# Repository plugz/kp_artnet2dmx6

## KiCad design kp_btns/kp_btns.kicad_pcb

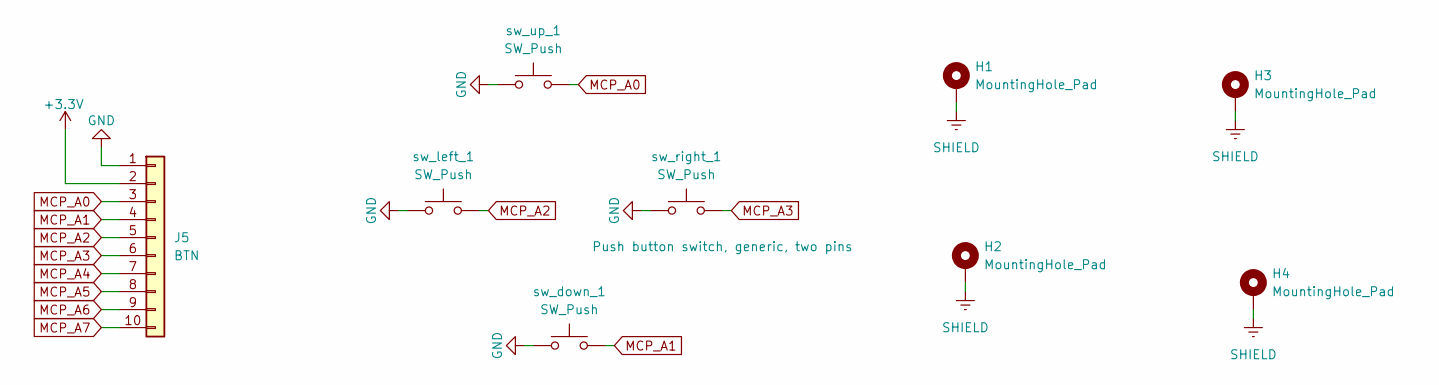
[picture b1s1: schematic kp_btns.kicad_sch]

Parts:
H1, H2, H3, H4: MountingHole_Pad; MountingHole_3.2mm_M3_Pad
J5: BTN; IDC-Header_2x05_P2.54mm_Vertical; JLCPCB Part # C5665
sw_down_1: SW_Push; SW_SPST_Omron_B3F-40xx
sw_left_1: SW_Push; SW_SPST_Omron_B3F-40xx
sw_right_1: SW_Push; SW_SPST_Omron_B3F-40xx
sw_up_1: SW_Push; SW_SPST_Omron_B3F-40xx

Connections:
+3.3V: J5.2
GND: J5.1, sw_down_1.1, sw_left_1.1, sw_right_1.1, sw_up_1.1
MCP_A0: J5.3, sw_up_1.2
MCP_A1: J5.4, sw_down_1.2
MCP_A2: J5.5, sw_left_1.2
MCP_A3: J5.6, sw_right_1.2
MCP_A4: J5.7
MCP_A5: J5.8
MCP_A6: J5.9
MCP_A7: J5.10
SHIELD: H1.1 (1_1), H2.1 (1_1), H3.1 (1_1), H4.1 (1_1)

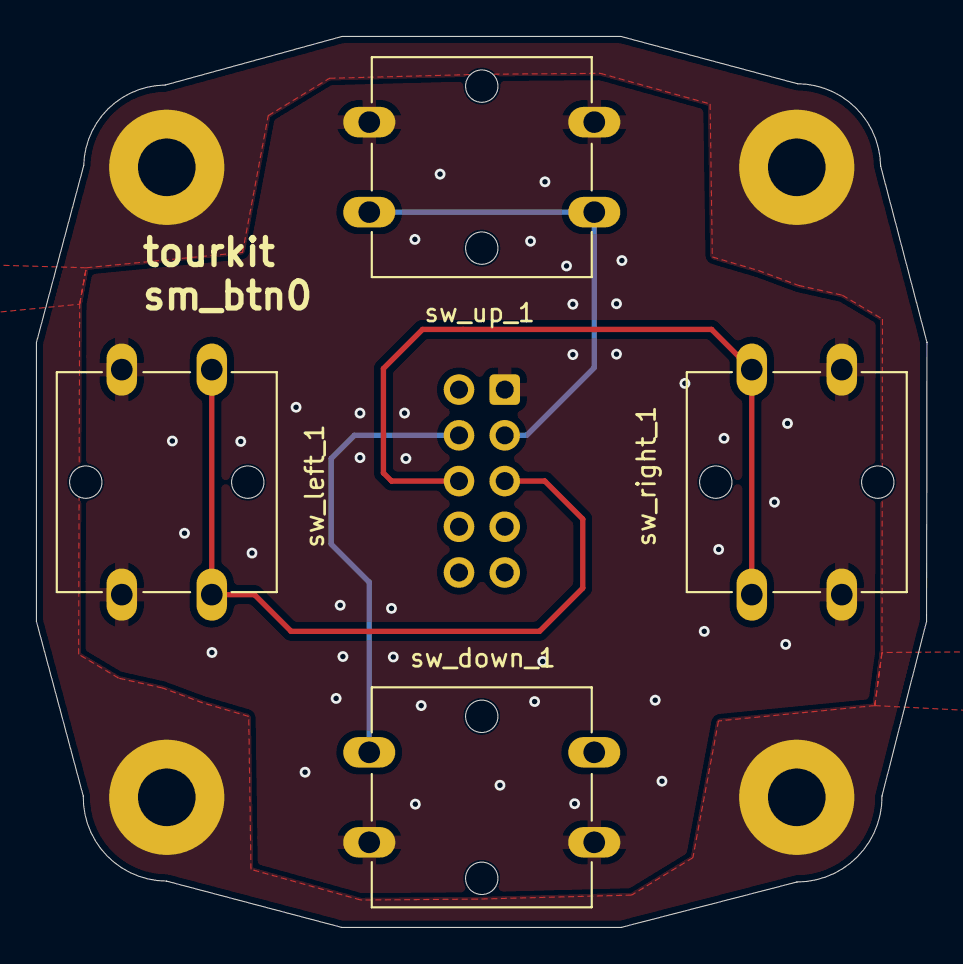
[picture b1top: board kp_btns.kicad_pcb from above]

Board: 2 copper layers, 49.5 x 49.5 mm, 9 parts (1 on the bottom side), 6 nets.

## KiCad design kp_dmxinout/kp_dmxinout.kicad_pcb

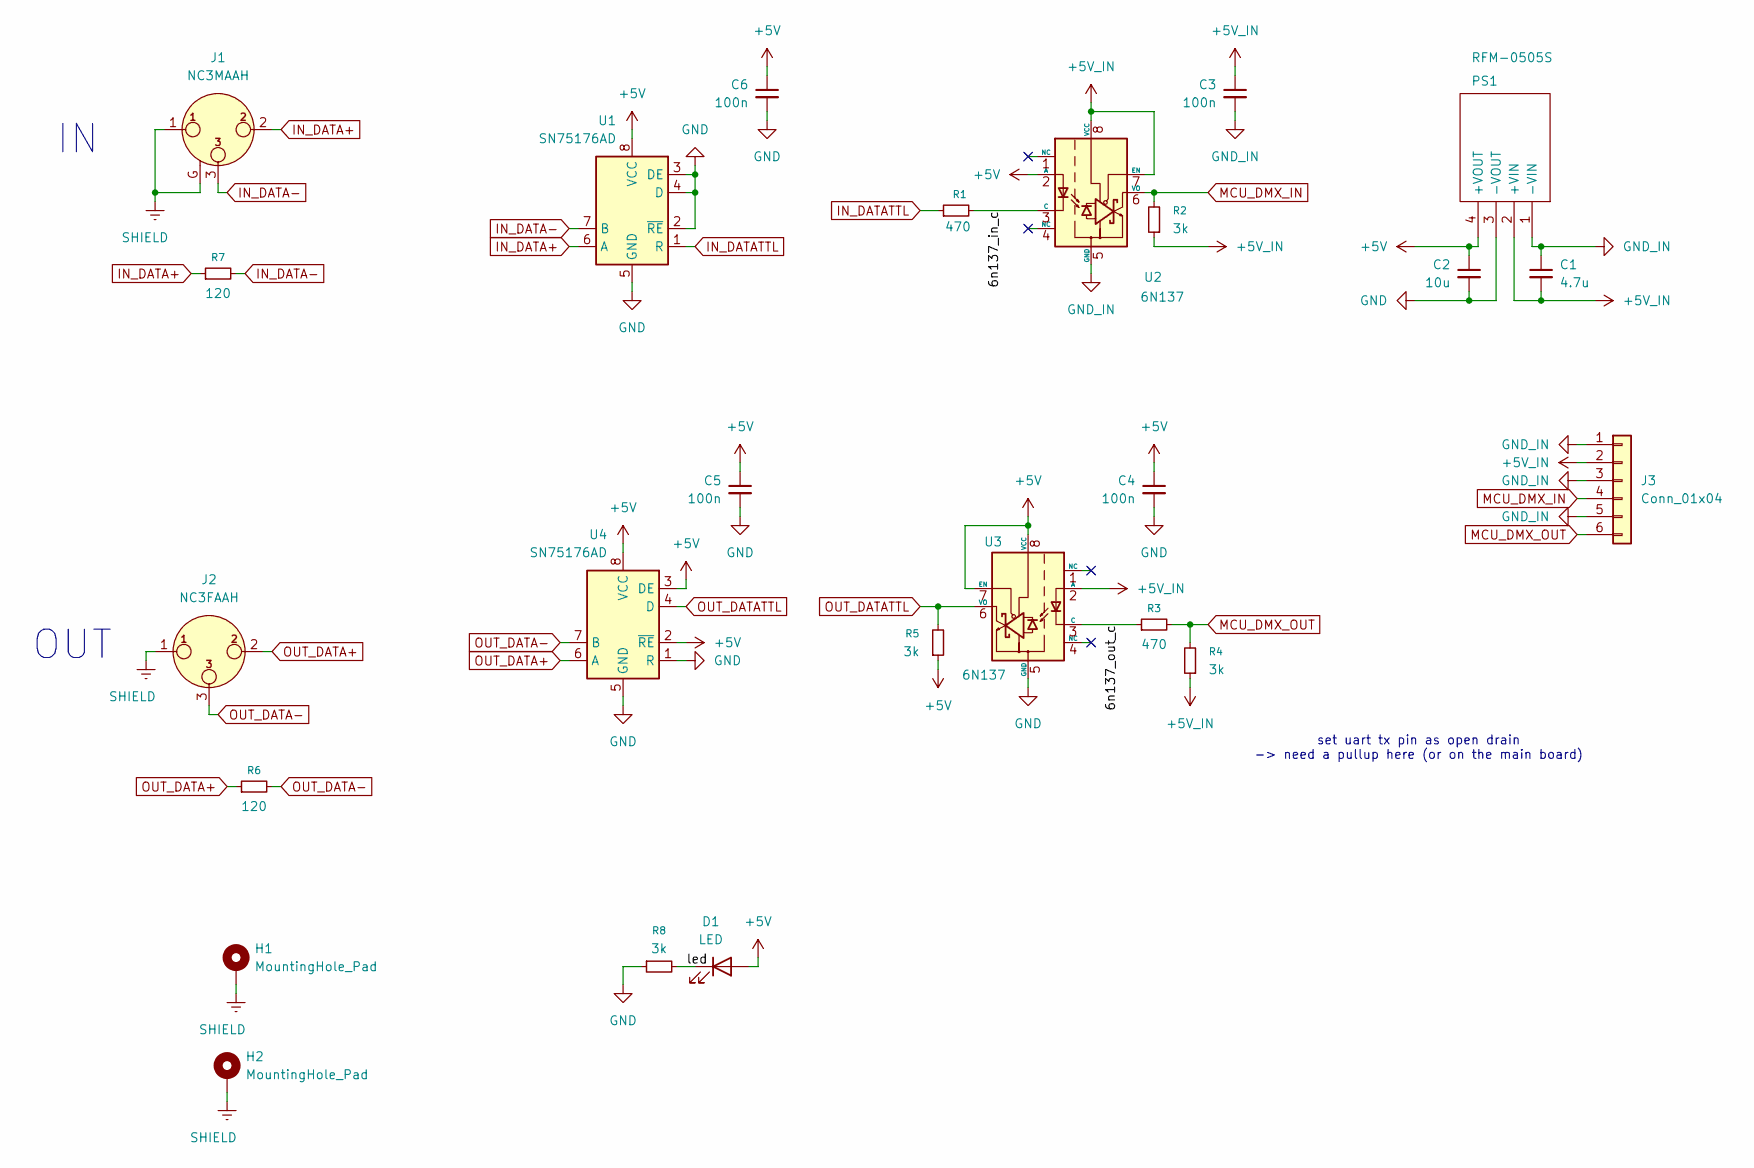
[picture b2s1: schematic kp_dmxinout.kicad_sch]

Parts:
C1: 4.7u; C_1206_3216Metric; LCSC C51205
C2: 10u; C_1206_3216Metric; LCSC C13585
C3, C4, C5, C6: 100n; C_0402_1005Metric; LCSC C1525
D1: LED; LED_0805_2012Metric; LCSC C965812
H1, H2: MountingHole_Pad; MountingHole_3.2mm_M3_Pad_Via
J1: NC3MAAH; Jack_XLR_Neutrik_NC3MAAH_Horizontal; LCSC C368463
J2: NC3FAAH; Jack_XLR_Neutrik_NC3FAAH_Horizontal; LCSC C368521
J3: Conn_01x04; IDC-Header_2x03_P2.54mm_Vertical; LCSC C11214
PS1: RFM-0505S; RFM0505S; Manufacturer_Part_Number RFM-0505S; LCSC C22371855
R1, R3: 470; R_0603_1608Metric; LCSC C844786
R2, R4, R5, R8: 3k; R_0805_2012Metric; LCSC C126350
R6, R7: 120; R_0603_1608Metric; LCSC C844736
U1, U4: SN75176AD; SOIC-8_3.9x4.9mm_P1.27mm; LCSC C468242
U2, U3: 6N137; DIP-8_W7.62mm; LCSC C142297

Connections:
+5V: C2.1, C4.1, C5.1, C6.1, D1.2 (A), PS1.4 (+VOUT), R5.1, U1.8 (VCC), U2.2 (A), U3.7 (EN), U3.8 (VCC), U4.2 (~RE), U4.3 (DE), U4.8 (VCC)
+5V_IN: C1.2, C3.1, J3.2, PS1.2 (+VIN), R2.1, R4.1, U2.7 (EN), U2.8 (VCC), U3.2 (A)
/6n137_in_c: R1.2, U2.3 (C)
/6n137_out_c: R3.1, U3.3 (C)
/led: D1.1 (K), R8.2
GND: C2.2, C4.2, C5.2, C6.2, PS1.3 (-VOUT), R8.1, U1.2 (~RE), U1.3 (DE), U1.4 (D), U1.5 (GND), U3.5 (GND), U4.1 (R), U4.5 (GND)
GND_IN: C1.1, C3.2, J3.1, J3.3, J3.5, PS1.1 (-VIN), U2.5 (GND)
IN_DATA+: J1.2, R7.1, U1.6 (A)
IN_DATA-: J1.3, R7.2, U1.7 (B)
IN_DATATTL: R1.1, U1.1 (R)
MCU_DMX_IN: J3.4, R2.2, U2.6 (VO)
MCU_DMX_OUT: J3.6, R3.2, R4.2
OUT_DATA+: J2.2, R6.1, U4.6 (A)
OUT_DATA-: J2.3, R6.2, U4.7 (B)
OUT_DATATTL: R5.2, U3.6 (VO), U4.4 (D)
SHIELD: H1.1 (1_1), H2.1 (1_1), J1.1, J1.G, J2.1

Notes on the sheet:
set uart tx pin as open drain -> need a pullup here (or on the main board)
OUT

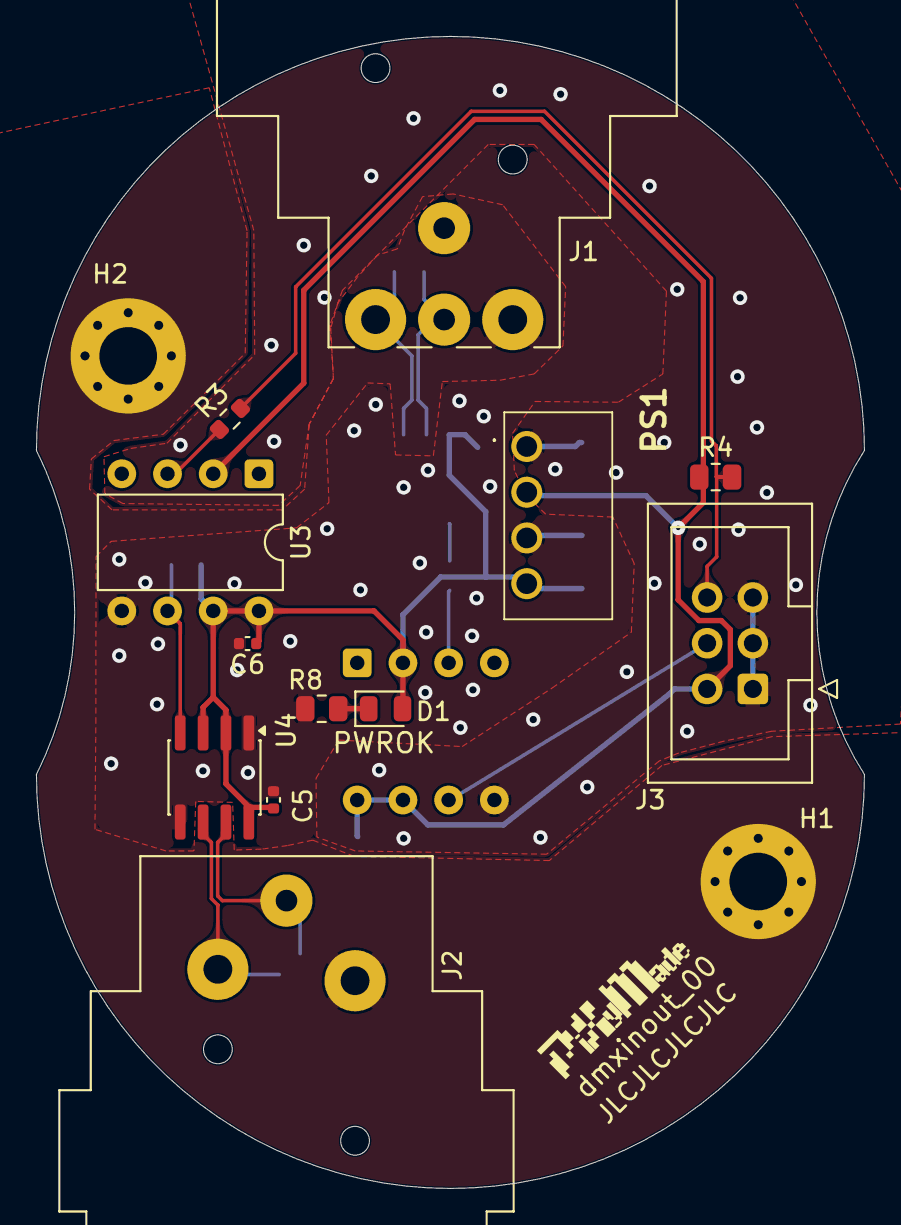
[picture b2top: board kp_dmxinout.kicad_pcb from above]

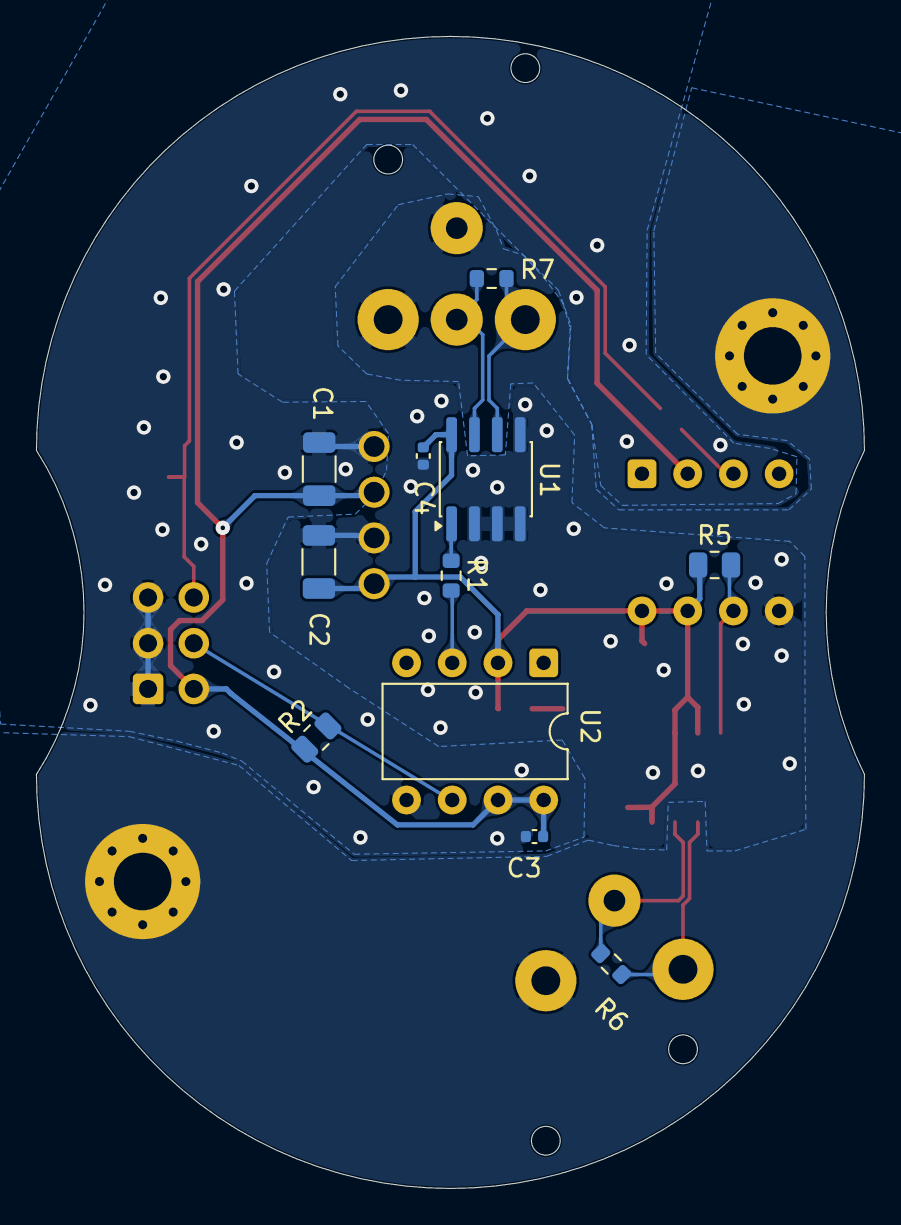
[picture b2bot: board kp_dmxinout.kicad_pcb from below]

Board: 2 copper layers, 46.0 x 64.0 mm, 25 parts (11 on the bottom side), 16 nets.

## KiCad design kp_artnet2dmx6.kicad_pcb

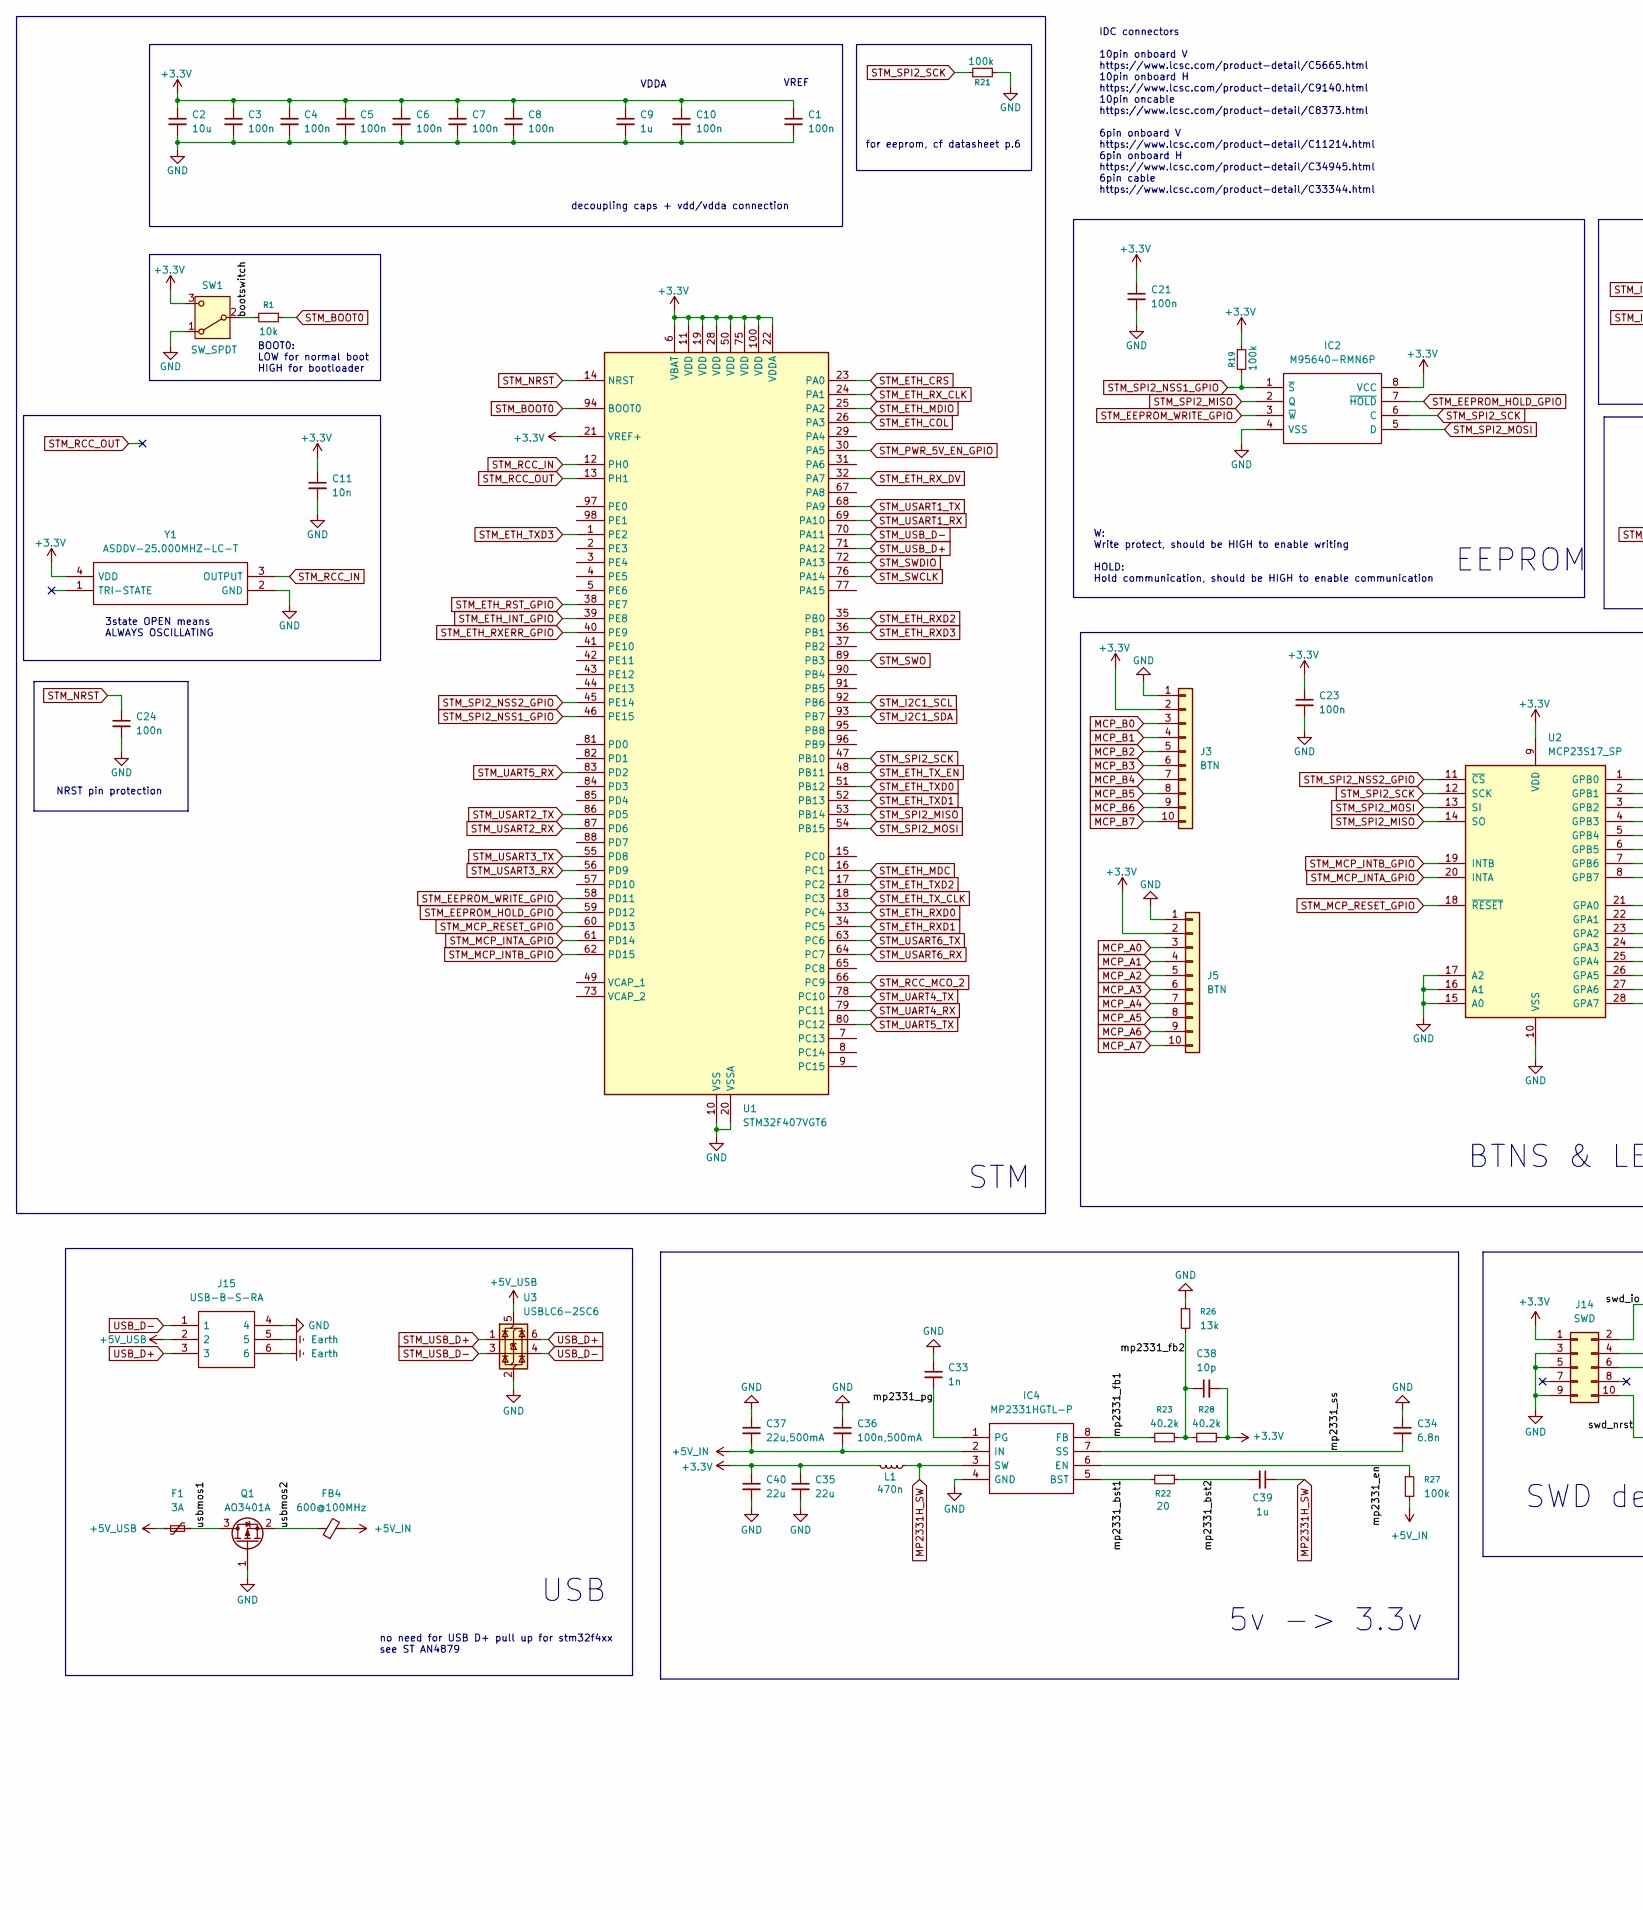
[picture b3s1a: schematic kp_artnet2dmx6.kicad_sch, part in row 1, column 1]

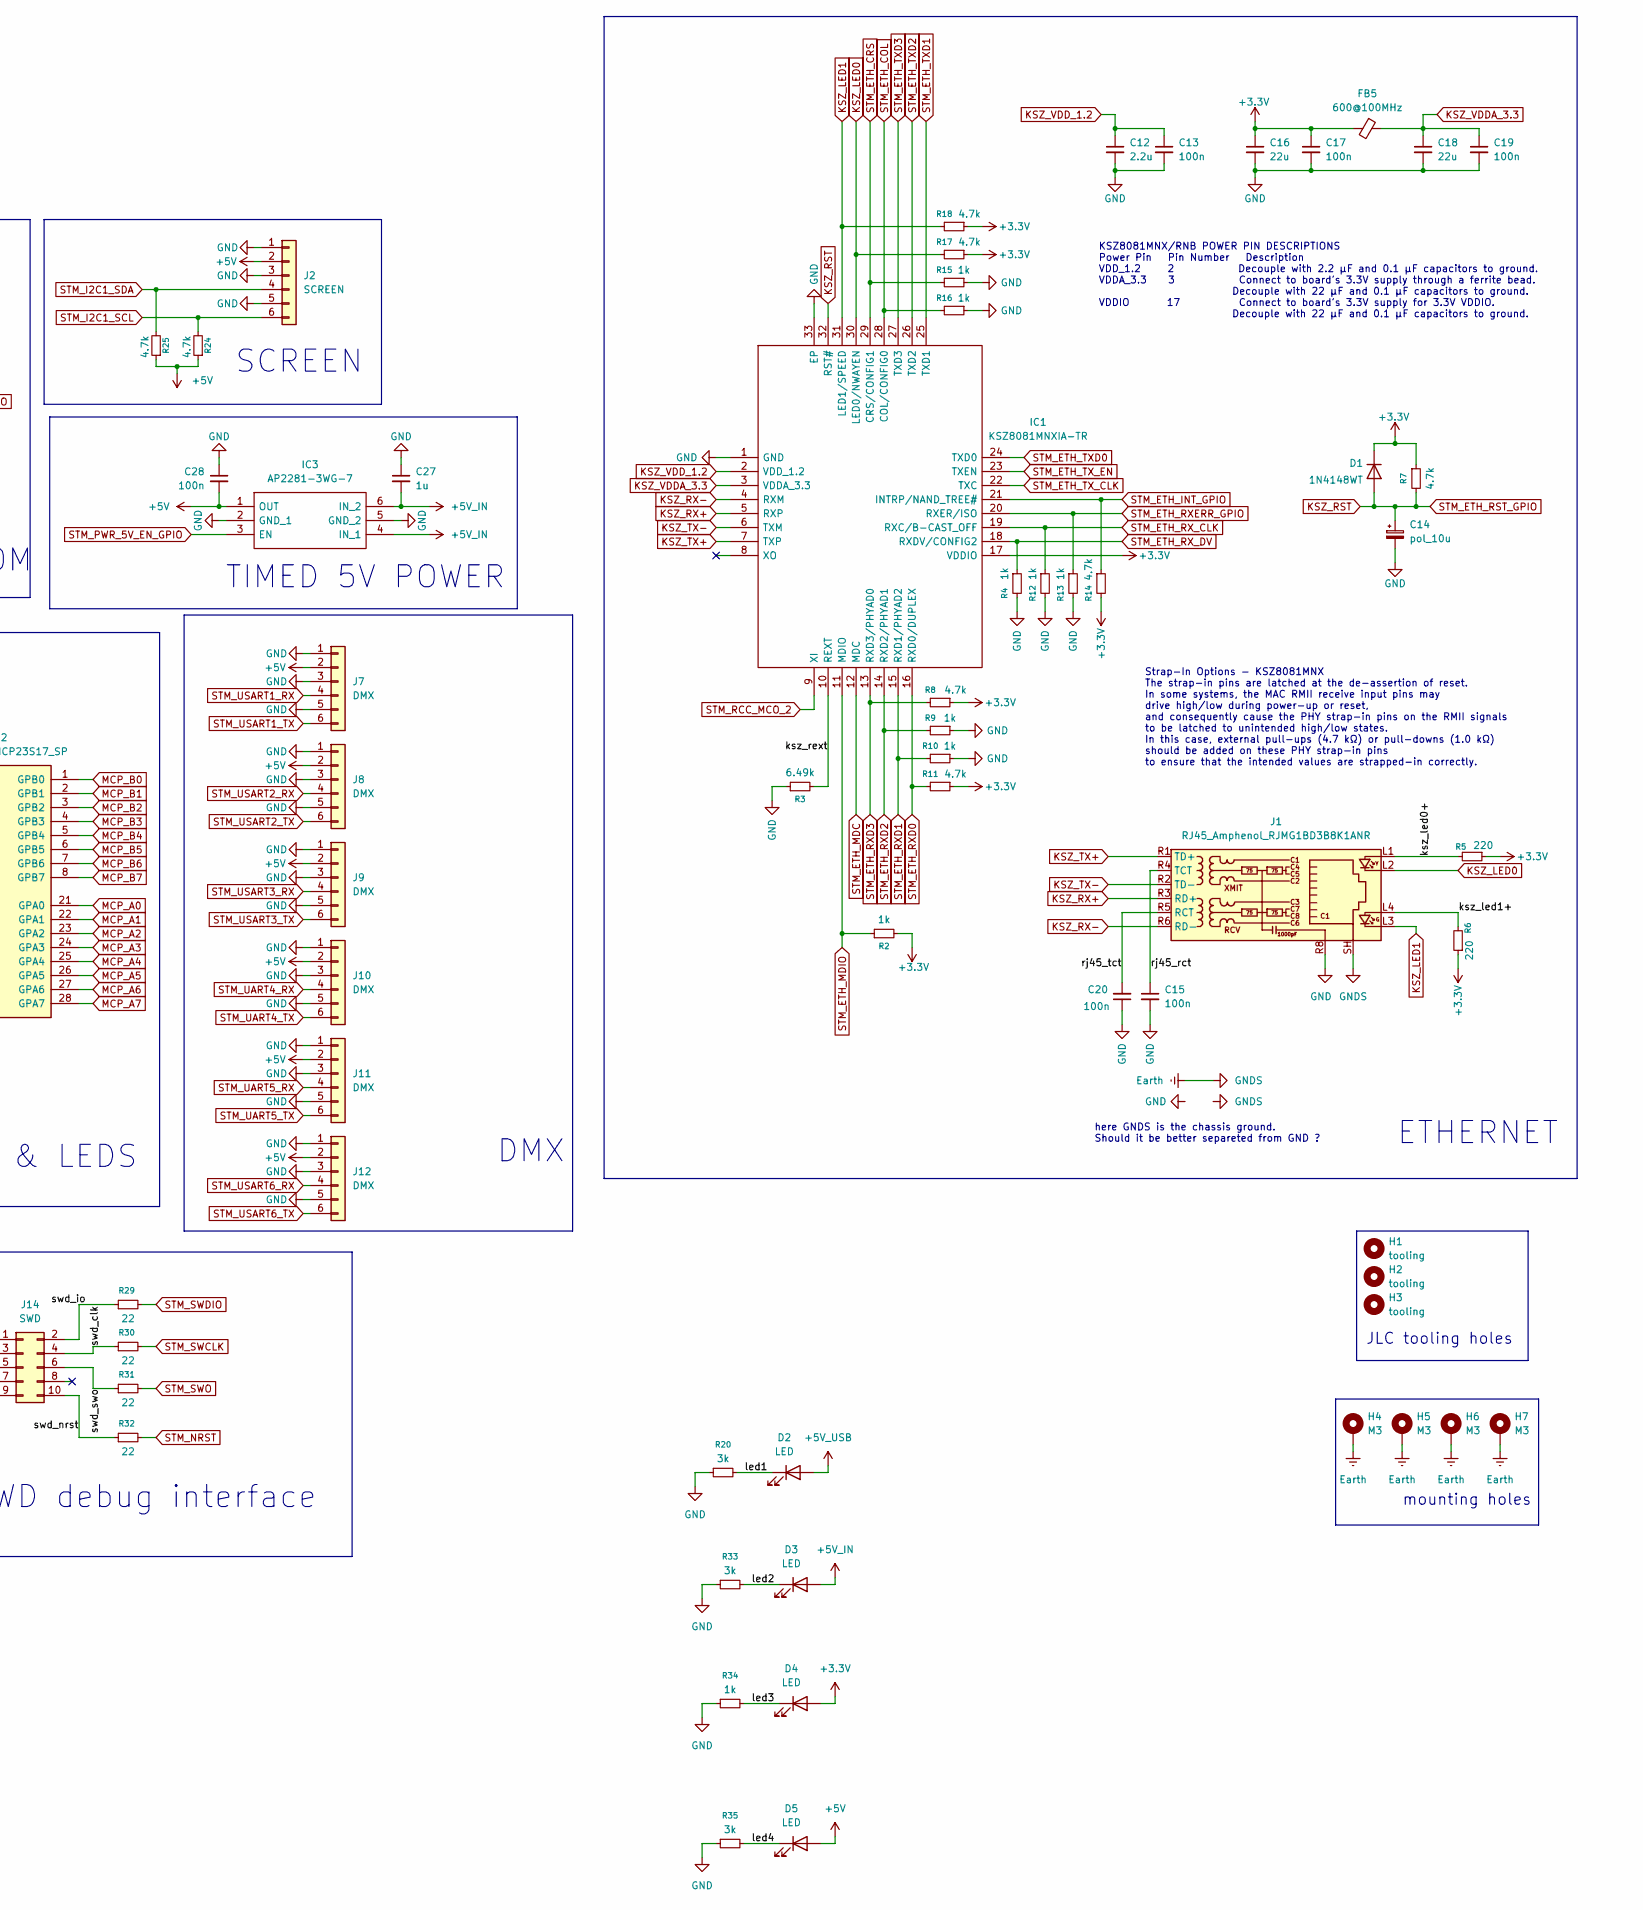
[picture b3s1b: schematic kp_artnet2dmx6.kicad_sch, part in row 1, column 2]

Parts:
C1, C3, C4, C5, C6, C7, C8, C10, C13, C15, C17, C19, C20, C21, C23, C24, C28: 100n; C_0402_1005Metric; JLCPCB Part # C1525
C2: 10u; C_1206_3216Metric; JLCPCB Part # C9807
C9, C27, C39: 1u; C_0805_2012Metric; JLCPCB Part # C24123
C11: 10n; C_0402_1005Metric; JLCPCB Part # C15195
C12: 2.2u; C_0805_2012Metric; JLCPCB Part # C19110
C14: pol_10u; C_0603_1608Metric; JLCPCB Part # C2158420
C16, C18, C35, C40: 22u; C_1206_3216Metric; JLCPCB Part # C5177178
C33: 1n; C_0402_1005Metric; JLCPCB Part # C14442
C34: 6.8n; C_0402_1005Metric; JLCPCB Part # C161171
C36: 100n,500mA; C_0402_1005Metric; JLCPCB Part # C1525
C37: 22u,500mA; C_1206_3216Metric; JLCPCB Part # C5177178
C38: 10p; C_0402_1005Metric; JLCPCB Part # C32949
D1: 1N4148WT; D_SOD-523; JLCPCB Part # C232841
D2, D3, D4, D5: LED; LED_0805_2012Metric
F1: 3A; Fuse_1812_4532Metric; JLCPCB Part # C18198349
FB4, FB5: 600@100MHz; L_1206_3216Metric; JLCPCB Part # C2858472
H1, H2, H3: tooling; ToolingHole_1.152mm
H4, H5, H6, H7: M3; MountingHole_3.2mm_M3_Pad_Via
IC1: KSZ8081MNXIA-TR; QFN50P500X500X100-33N-D; Mouser Part Number 998-KSZ8081MNXIATR
IC2: M95640-RMN6P; SOIC127P600X175-8N; Manufacturer_Part_Number M95640-RMN6P
IC3: AP2281-3WG-7; SOT95P285X140-6N; Manufacturer_Part_Number AP2281-3WG-7; JLCPCB Part # C128634
IC4: MP2331HGTL-P; MP2331HGTLP; Manufacturer_Part_Number MP2331HGTL-P; Mouser Part Number 946-MP2331HGTL-P
J1: RJ45_Amphenol_RJMG1BD3B8K1ANR
J2: SCREEN; IDC-Header_2x03_P2.54mm_Vertical
J3, J5: BTN; IDC-Header_2x05_P2.54mm_Vertical
J7, J8, J9, J10, J11, J12: DMX; IDC-Header_2x03_P2.54mm_Vertical
J14: SWD; PinSocket_2x05_P1.27mm_Vertical_SMD
J15: USB-B-S-RA; USBBSRA; Manufacturer_Part_Number USB-B-S-RA
L1: 470n; L_Bourns_SRP4020CC
Q1: AO3401A; SOT-23; JLCPCB Part # C15127
R1: 10k; R_0603_1608Metric; JLCPCB Part # C844918
R2, R4, R9, R10, R12, R13, R15, R16, R34: 1k; R_0603_1608Metric; JLCPCB Part # C844920
R3: 6.49k; R_0805_2012Metric; JLCPCB Part # C2933484
R5, R6: 220; R_0805_2012Metric; JLCPCB Part # C2933537
R7, R8, R11, R14, R17, R18, R24, R25: 4.7k; R_0603_1608Metric; JLCPCB Part # C23162
R19, R21, R27: 100k; R_0603_1608Metric; JLCPCB Part # C2907088
R20, R33, R35: 3k; R_0805_2012Metric
R22: 20; R_0805_2012Metric; JLCPCB Part # C17544
R23, R28: 40.2k; R_0805_2012Metric; JLCPCB Part # C17678
R26: 13k; R_0805_2012Metric; JLCPCB Part # C17455
R29, R30, R31, R32: 22; R_0805_2012Metric; JLCPCB Part # C17561
SW1: SW_SPDT; SW_SPDT_PCM12
U1: STM32F407VGT6; LQFP-100_14x14mm_P0.5mm; JLCPCB Part # C12345
U2: MCP23S17_SP; DIP-28_W7.62mm; farnell link already have
U3: USBLC6-2SC6; SOT-23-6; JLCPCB Part # C7519
Y1: ASDDV-25.000MHZ-LC-T; AbraconASDDV; Manufacturer_Part_Number ASDDV-25.000MHZ-LC-T; Mouser Part Number 815-ASDDV-2500MHZLCT

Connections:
+3.3V: C1.1, C2.1, C3.1, C4.1, C5.1, C6.1, C7.1, C8.1, C9.1, C10.1, C11.1, C16.1, C17.1, C21.1, C23.1, C35.1, C38.2, C40.1, D1.1 (K), D4.2 (A), FB5.2, IC1.17 (VDDIO), IC2.8 (VCC), J3.2, J5.2, J14.1, L1.2, R2.2, R5.1, R6.1, R7.1, R8.1, R11.1, R14.2, R17.1, R18.1, R19.1, R28.2, SW1.3 (C), U1.6 (VBAT), U1.11 (VDD), U1.19 (VDD), U1.21 (VREF+), U1.22 (VDDA), U1.28 (VDD), U1.50 (VDD), U1.75 (VDD), U1.100 (VDD), U2.9 (VDD), Y1.4 (VDD)
+5V: C28.2, D5.2 (A), IC3.1 (OUT), J2.2, J7.2, J8.2, J9.2, J10.2, J11.2, J12.2, R24.1, R25.1
+5V_IN: C27.2, C36.2, C37.2, D3.2 (A), FB4.2, IC3.4 (IN_1), IC3.6 (IN_2), IC4.2 (IN), R27.2
+5V_USB: D2.2 (A), F1.1, J15.2, U3.5 (VBUS)
/bootswitch: R1.2, SW1.2 (B)
/ksz_led0+: J1.L1, R5.2
/ksz_led1+: J1.L4, R6.2
/ksz_rext: IC1.10 (REXT), R3.2
/led1: D2.1 (K), R20.2
/led2: D3.1 (K), R33.2
/led3: D4.1 (K), R34.2
/led4: D5.1 (K), R35.2
/mp2331_bst1: IC4.5 (BST), R22.2
/mp2331_bst2: C39.2, R22.1
/mp2331_en: IC4.6 (EN), R27.1
/mp2331_fb1: IC4.8 (FB), R23.1
/mp2331_fb2: C38.1, R23.2, R26.2, R28.1
/mp2331_pg: C33.2, IC4.1 (PG)
/mp2331_ss: C34.2, IC4.7 (SS)
/rj45_rct: C15.1, J1.R4 (TCT)
/rj45_tct: C20.2, J1.R5 (RCT)
/swd_clk: J14.4, R30.1
/swd_io: J14.2, R29.1
/swd_nrst: J14.10, R32.1
/swd_swo: J14.6, R31.1
/usbmos1: F1.2, Q1.3 (D)
/usbmos2: FB4.1, Q1.2 (S)
Earth: H4.1 (1_1), H5.1 (1_1), H6.1 (1_1), H7.1 (1_1), J1.SH, J15.5, J15.6
GND: C1.2, C2.2, C3.2, C4.2, C5.2, C6.2, C7.2, C8.2, C9.2, C10.2, C11.2, C12.2, C13.2, C14.2, C15.2, C16.2, C17.2, C18.2, C19.2, C20.1, C21.2, C23.2, C24.2, C27.1, C28.1, C33.1, C34.1, C35.2, C36.1, C37.1, C40.2, IC1.1 (GND), IC1.33 (EP), IC2.4 (VSS), IC3.2 (GND_1), IC3.5 (GND_2), IC4.4 (GND), J1.R8, J2.1, J2.3, J2.5, J3.1, J5.1, J7.1, J7.3, J7.5, J8.1, J8.3, J8.5, J9.1, J9.3, J9.5, J10.1, J10.3, J10.5, J11.1, J11.3, J11.5, J12.1, J12.3, J12.5, J14.3, J14.5, J14.9, J15.4, Q1.1 (G), R3.1, R4.2, R9.1, R10.1, R12.2, R13.2, R15.1, R16.1, R20.1, R21.2, R26.1, R33.1, R34.1, R35.1, SW1.1 (A), U1.10 (VSS), U1.20 (VSSA), U1.27 (VSS), U1.74 (VSS), U1.99 (VSS), U2.10 (VSS), U2.15 (A0), U2.16 (A1), U2.17 (A2), U3.2 (GND), Y1.2 (GND)
KSZ_LED0: IC1.30 (LED0/NWAYEN), J1.L2, R17.2
KSZ_LED1: IC1.31 (LED1/SPEED), J1.L3, R18.2
KSZ_RST: C14.1, D1.2 (A), IC1.32 (RST#), R7.2, U1.38 (PE7)
KSZ_RX+: IC1.5 (RXP), J1.R3 (RD+)
KSZ_RX-: IC1.4 (RXM), J1.R6 (RD-)
KSZ_TX+: IC1.7 (TXP), J1.R1 (TD+)
KSZ_TX-: IC1.6 (TXM), J1.R2 (TD-)
KSZ_VDDA_3.3: C18.1, C19.1, FB5.1, IC1.3 (VDDA_3.3)
KSZ_VDD_1.2: C12.1, C13.1, IC1.2 (VDD_1.2)
MCP_A0: J5.3, U2.21 (GPA0)
MCP_A1: J5.4, U2.22 (GPA1)
MCP_A2: J5.5, U2.23 (GPA2)
MCP_A3: J5.6, U2.24 (GPA3)
MCP_A4: J5.7, U2.25 (GPA4)
MCP_A5: J5.8, U2.26 (GPA5)
MCP_A6: J5.9, U2.27 (GPA6)
MCP_A7: J5.10, U2.28 (GPA7)
MCP_B0: J3.3, U2.1 (GPB0)
MCP_B1: J3.4, U2.2 (GPB1)
MCP_B2: J3.5, U2.3 (GPB2)
MCP_B3: J3.6, U2.4 (GPB3)
MCP_B4: J3.7, U2.5 (GPB4)
MCP_B5: J3.8, U2.6 (GPB5)
MCP_B6: J3.9, U2.7 (GPB6)
MCP_B7: J3.10, U2.8 (GPB7)
MP2331H_SW: C39.1, IC4.3 (SW), L1.1
STM_BOOT0: R1.1, U1.94 (BOOT0)
STM_EEPROM_HOLD_GPIO: IC2.7 (~HOLD), U1.59 (PD12)
STM_EEPROM_WRITE_GPIO: IC2.3 (~W), U1.58 (PD11)
STM_ETH_COL: IC1.28 (COL/CONFIG0), R16.2, U1.26 (PA3)
STM_ETH_CRS: IC1.29 (CRS/CONFIG1), R15.2, U1.23 (PA0)
STM_ETH_INT_GPIO: IC1.21 (INTRP/NAND_TREE#), R14.1, U1.39 (PE8)
STM_ETH_MDC: IC1.12 (MDC), U1.16 (PC1)
STM_ETH_MDIO: IC1.11 (MDIO), R2.1, U1.25 (PA2)
STM_ETH_RXD0: IC1.16 (RXD0/DUPLEX), R11.2, U1.33 (PC4)
STM_ETH_RXD1: IC1.15 (RXD1/PHYAD2), R10.2, U1.34 (PC5)
STM_ETH_RXD2: IC1.14 (RXD2/PHYAD1), R9.2, U1.35 (PB0)
STM_ETH_RXD3: IC1.13 (RXD3/PHYAD0), R8.2, U1.36 (PB1)
STM_ETH_RXERR_GPIO: IC1.20 (RXER/ISO), R13.1, U1.40 (PE9)
STM_ETH_RX_CLK: IC1.19 (RXC/B-CAST_OFF), R12.1, U1.24 (PA1)
STM_ETH_RX_DV: IC1.18 (RXDV/CONFIG2), R4.1, U1.32 (PA7)
STM_ETH_TXD0: IC1.24 (TXD0), U1.51 (PB12)
STM_ETH_TXD1: IC1.25 (TXD1), U1.52 (PB13)
STM_ETH_TXD2: IC1.26 (TXD2), U1.17 (PC2)
STM_ETH_TXD3: IC1.27 (TXD3), U1.1 (PE2)
STM_ETH_TX_CLK: IC1.22 (TXC), U1.18 (PC3)
STM_ETH_TX_EN: IC1.23 (TXEN), U1.48 (PB11)
STM_I2C1_SCL: J2.6, R24.2, U1.92 (PB6)
STM_I2C1_SDA: J2.4, R25.2, U1.93 (PB7)
STM_MCP_INTA_GPIO: U1.61 (PD14), U2.20 (INTA)
STM_MCP_INTB_GPIO: U1.62 (PD15), U2.19 (INTB)
STM_MCP_RESET_GPIO: U1.60 (PD13), U2.18 (~RESET)
STM_NRST: C24.1, R32.2, U1.14 (NRST)
STM_PWR_5V_EN_GPIO: IC3.3 (EN), U1.30 (PA5)
STM_RCC_IN: U1.12 (PH0), Y1.3 (OUTPUT)
STM_RCC_MCO_2: IC1.9 (XI), U1.66 (PC9)
STM_RCC_OUT: U1.13 (PH1)
STM_SPI2_MISO: IC2.2 (Q), U1.53 (PB14), U2.14 (SO)
STM_SPI2_MOSI: IC2.5 (D), U1.54 (PB15), U2.13 (SI)
STM_SPI2_NSS1_GPIO: IC2.1 (~S), R19.2, U1.46 (PE15)
STM_SPI2_NSS2_GPIO: U1.45 (PE14), U2.11 (~CS)
STM_SPI2_SCK: IC2.6 (C), R21.1, U1.47 (PB10), U2.12 (SCK)
STM_SWCLK: R30.2, U1.76 (PA14)
STM_SWDIO: R29.2, U1.72 (PA13)
STM_SWO: R31.2, U1.89 (PB3)
STM_UART4_RX: J10.4, U1.79 (PC11)
STM_UART4_TX: J10.6, U1.78 (PC10)
STM_UART5_RX: J11.4, U1.83 (PD2)
STM_UART5_TX: J11.6, U1.80 (PC12)
STM_USART1_RX: J7.4, U1.69 (PA10)
STM_USART1_TX: J7.6, U1.68 (PA9)
STM_USART2_RX: J8.4, U1.87 (PD6)
STM_USART2_TX: J8.6, U1.86 (PD5)
STM_USART3_RX: J9.4, U1.56 (PD9)
STM_USART3_TX: J9.6, U1.55 (PD8)
STM_USART6_RX: J12.4, U1.64 (PC7)
STM_USART6_TX: J12.6, U1.63 (PC6)
STM_USB_D+: U1.71 (PA12), U3.1 (I/O1)
STM_USB_D-: U1.70 (PA11), U3.3 (I/O2)
USB_D+: J15.3, U3.6 (I/O1)
USB_D-: J15.1, U3.4 (I/O2)

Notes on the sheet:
DMX
SWD debug interface
5v -> 3.3v
KSZ8081MNX/RNB POWER PIN DESCRIPTIONS Power Pin Pin Number Description VDD_1.2 2 Decouple with 2.2 μF and 0.1 μF capacitors to ground. VDDA_3.3 3 Connect to board's 3.3V supply through a ferrite bead. Decouple with 22 μF and 0.1 μF capacitors to ground. VDDIO 17 Connect to board's 3.3V supply for 3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
BTNS & LEDS
here GNDS is the chassis ground. Should it be better separeted from GND ?
SCREEN
EEPROM
USB
for eeprom, cf datasheet p.6
W: Write protect, should be HIGH to enable writing HOLD: Hold communication, should be HIGH to enable communication
VDDA
JLC tooling holes
IDC connectors 10pin onboard V https://www.lcsc.com/product-detail/C5665.html 10pin onboard H https://www.lcsc.com/product-detail/C9140.html 10pin oncable https://www.lcsc.com/product-detail/C8373.html 6pin onboard V https://www.lcsc.com/product-detail/C11214.html 6pin onboard H https://www.lcsc.co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
VREF
TIMED 5V POWER
STM
decoupling caps + vdd/vdda connection
3state OPEN means ALWAYS OSCILLATING
ETHERNET
BOOT0: LOW for normal boot HIGH for bootloader
NRST pin protection
Strap-In Options - KSZ8081MNX The strap-in pins are latched at the de-assertion of reset. In some systems, the MAC RMII receive input pins may drive high/low during power-up or reset, and consequently cause the PHY strap-in pins on the RMII signals to be latched to unintended high/low states. In th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
mounting holes
no need for USB D+ pull up for stm32f4xx see ST AN4879

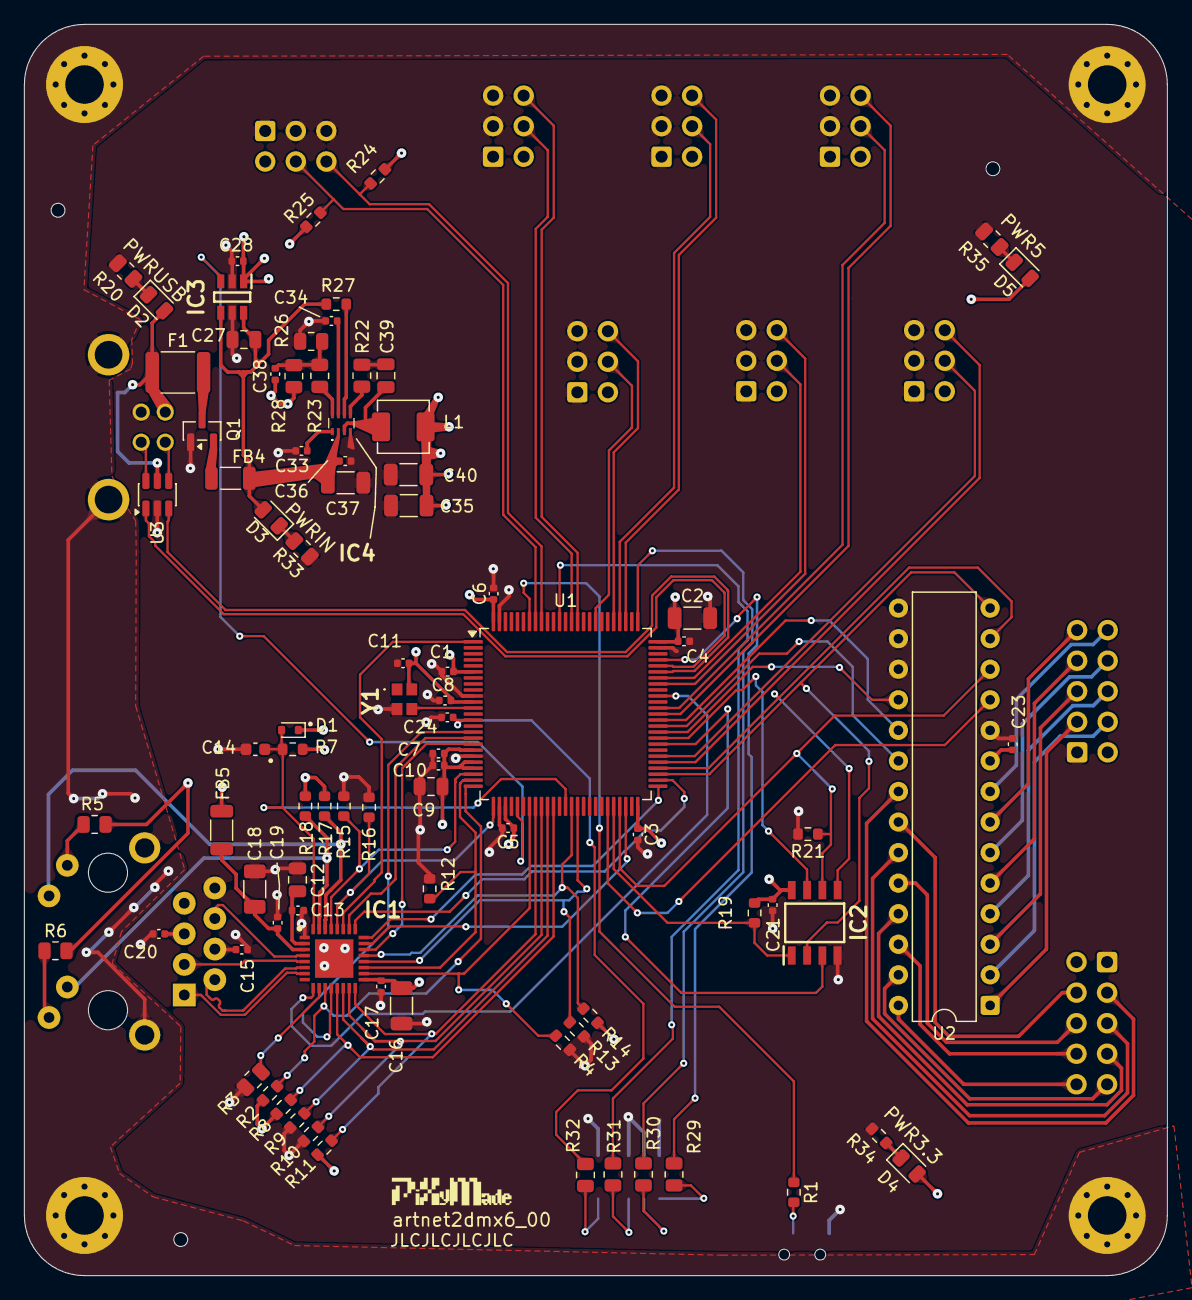
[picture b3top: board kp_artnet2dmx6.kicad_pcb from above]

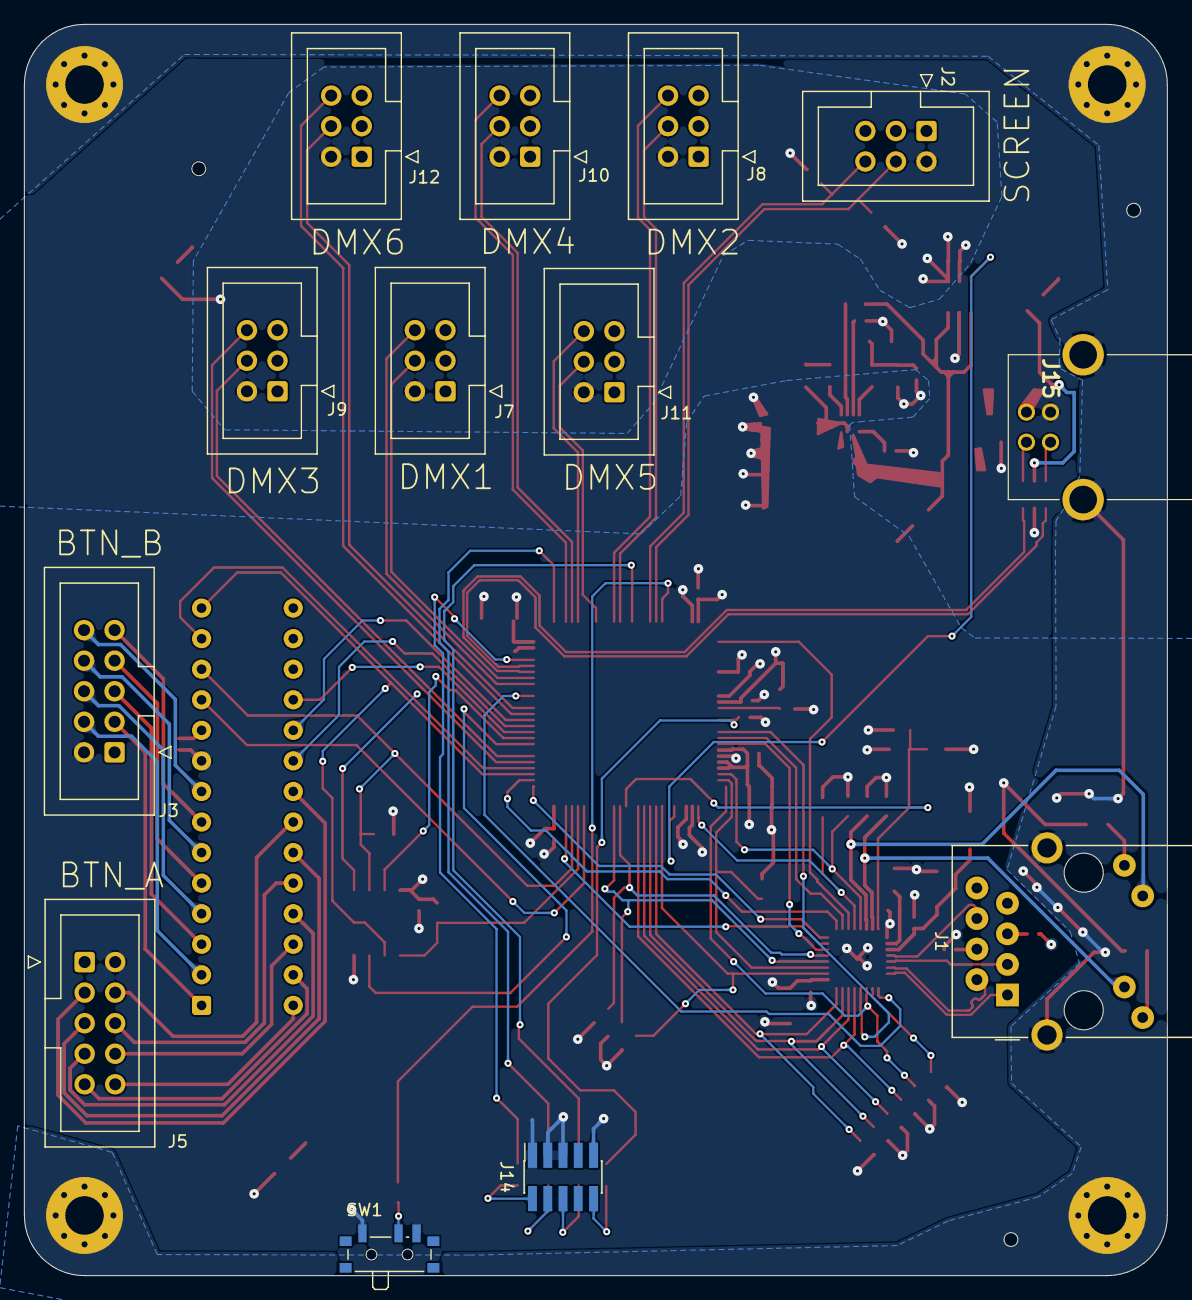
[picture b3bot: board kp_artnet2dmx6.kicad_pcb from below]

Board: 4 copper layers, 95.0 x 104.0 mm, 106 parts (13 on the bottom side), 109 nets.

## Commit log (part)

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2026-02-15 add empty kicad project
2026-02-16 add stm32
2026-02-18 add cubemx file
2026-02-18 sch: add phy, add oscillator
2026-02-18 add ksz eth controller, todo finish connecting it
2026-02-20 connect ksz
2026-02-26 ioc: add lwip
2026-02-26 add eeprom
2026-02-26 connect eeprom
2026-02-27 add mcp
2026-02-27 add level shifter for i2c screen
2026-03-01 use delayed 5v supply, add dmxinout board
2026-03-01 connect usb
2026-03-24 sch: swd debug interface
2026-03-24 footprints - the beginning
2026-03-25 all footprints assigned
2026-03-25 fix usb conn
2026-03-25 start placing pcb
2026-03-26 fill buy links
2026-03-26 cubemx: stm32f407VET -> stm32f407VGT
2026-04-13 update to kicad 10
2026-04-16 start assigning netclasses
2026-04-17 main pcb : everything is connected
2026-04-21 fix drc errors
2026-04-21 schematic: change connectors from jst xh to IDC
2026-04-21 sch: remove caps on connectors
2026-04-21 pcb: change connectors to IDC
2026-04-21 dmxinout: do board
2026-04-22 dmx: disconnect shield & gnd
2026-04-24 main board : start doing sig gnd gnd sigpow
2026-04-25 DRC OK
2026-04-25 add pwr leds
2026-04-26 Revert "cubemx: stm32f407VET -> stm32f407VGT"
    This reverts commit 2003c71da7baa62a417fca543b3340f338673223.
2026-04-26 ready 4 prod
2026-04-26 add btn board
2026-04-26 fabrication order launched
2026-05-13 fix L1 footprint
